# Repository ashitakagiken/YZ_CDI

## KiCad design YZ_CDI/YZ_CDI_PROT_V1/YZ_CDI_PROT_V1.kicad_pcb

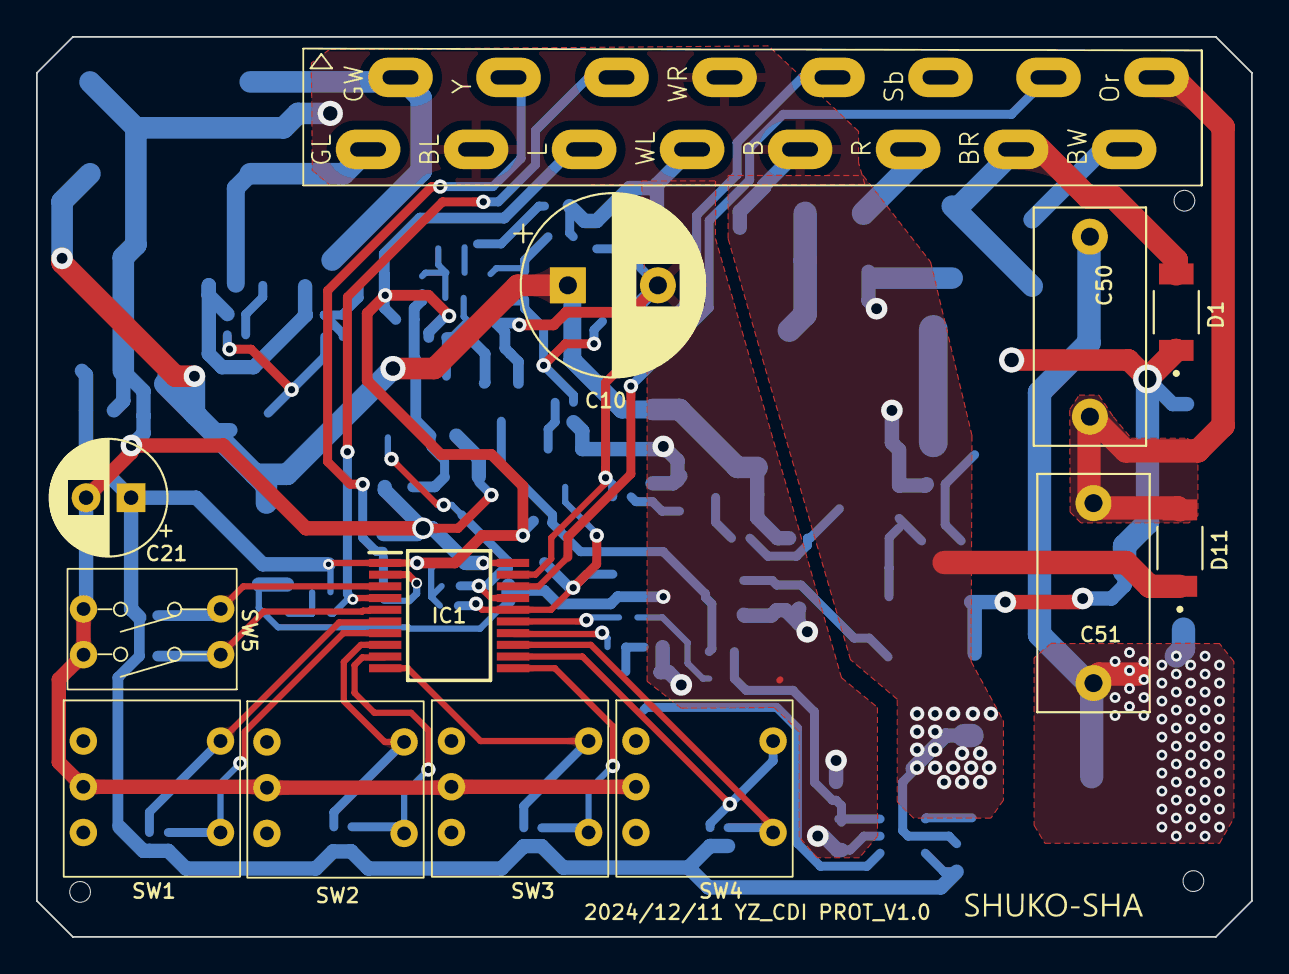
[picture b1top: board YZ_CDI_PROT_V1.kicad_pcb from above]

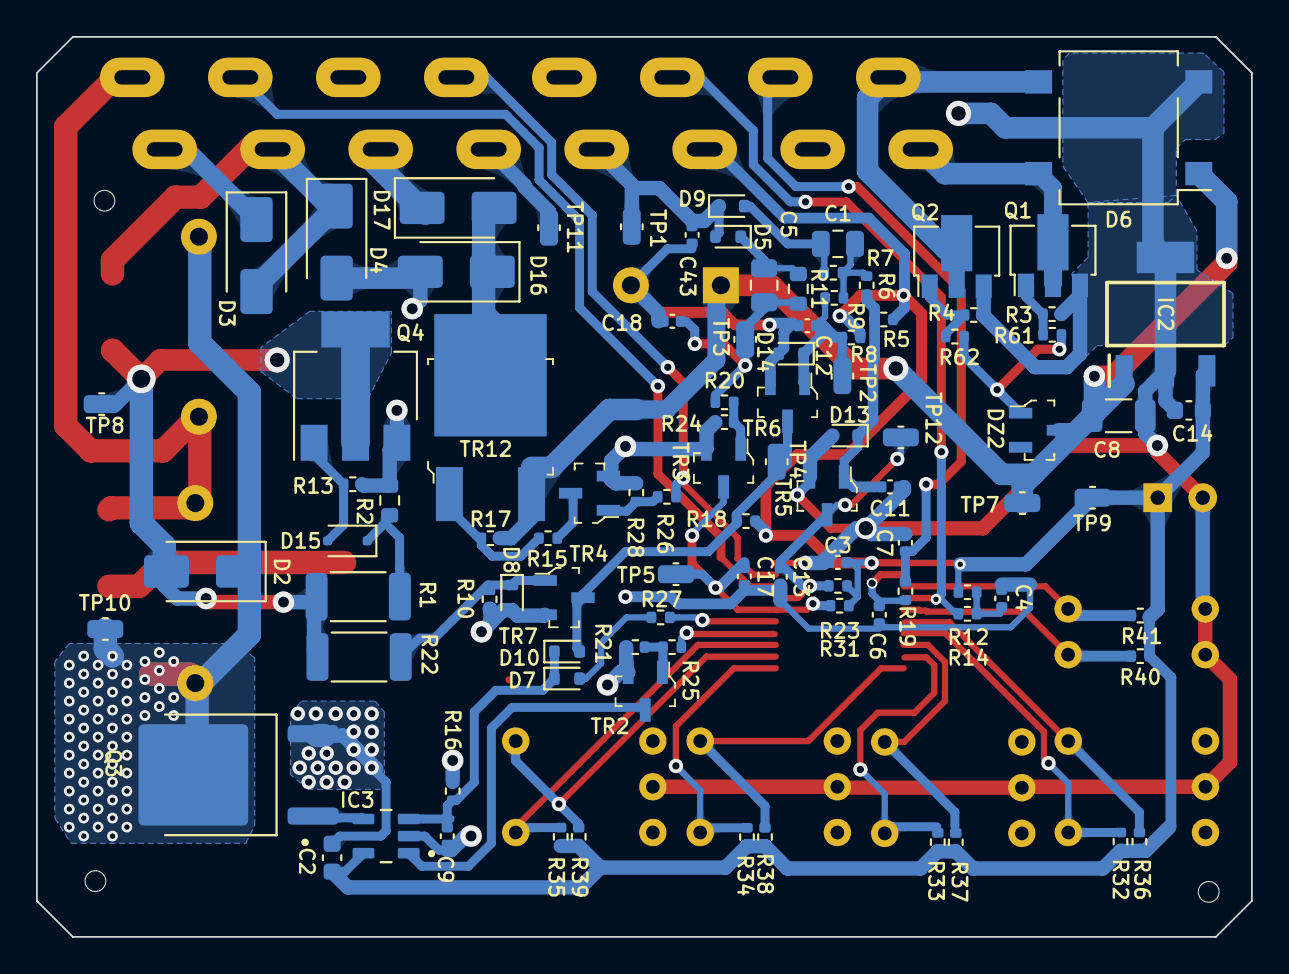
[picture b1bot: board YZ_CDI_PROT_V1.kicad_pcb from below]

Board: 2 copper layers, 67.5 x 50.0 mm, 109 parts (96 on the bottom side), 55 nets.

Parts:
C1: 2.2uF; C_0805_2012Metric
C2: 1uF; C_0603_1608Metric
C3, C6, C7, C11, C12, C17: 0.1uF; C_0402_1005Metric
C4, C9, C13, C18, C43: 10nF; C_0402_1005Metric
C5: 0.47uF; C_0805_2012Metric
C8: 10uF; C_1206_3216Metric
C10: 35V 270uF; CP_Radial_D10.0mm_P5.00mm
C14: 10uF; C_0603_1608Metric
C21: 16V 100uF; CP_Radial_D6.3mm_P2.50mm
C50, C51: 250V 1uF; C_Rect_L13.0mm_W6.0mm_P10.00mm_FKS3_FKP3_MKS4
CN1: FP-C-R16M
D1, D11: TSD3JFSH; SODFL4725X110N
D2, D3, D4, D16, D17: S1J; D_SMA
D5, D7, D8, D9, D10, D13, D14: RB501SM-30FH; D_SOD-523
D6: DF01S; Diode_Bridge_OnSemi_SDIP-4L
D15: BZX100A,115; D_SOD-323F
DZ2: BZX84C9V1LT1G; SOT-23-3
IC1: PIC16F15245-I_SS; SOP65P780X200-20N
IC2: TPS7B6950QDCYRQ1; SOT230P700X180-4N
IC3: UCC27519AQDBVRQ1; SOT95P280X145-5N
Q1, Q2: ZXMN6A11ZTA; SOT-89-3
Q3: RGPR30BM40; DPAK228P990X239-4N
Q4: IPN50R3K0CE; SOT-223-3_TabPin2
R1, R22: 200k 1/2W; R_2010_5025Metric
R2: 200K; R_0603_1608Metric
R3, R4, R12, R32, R33, R34, R35, R36, R37, R38, R39, R40, R41: 10k; R_0402_1005Metric
R5, R8, R13: 15k; R_0402_1005Metric
R6, R9, R15, R18, R27, R31: 2.2k; R_0402_1005Metric
R7: 22k; R_0402_1005Metric
R10, R20, R21, R25, R26, R28, R61, R62: 5.1k; R_0402_1005Metric
R11: 200k; R_0603_1608Metric
R14: 470; R_0402_1005Metric
R16, R17: 4.7k; R_0402_1005Metric
R19: 1k; R_0402_1005Metric
R23: 1.5k; R_0402_1005Metric
R24: 3.3k; R_0402_1005Metric
SW1, SW2, SW3, SW4: 42J04
SW5: EDS102SZ
TP1: WL PU; CheckPoint_1608Metric
TP2: PU2 BASE; CheckPoint_1608Metric
TP3: PU1 BASE; CheckPoint_1608Metric
TP4: PU2 INPUT; CheckPoint_1608Metric
TP5: PU1 INPUT; CheckPoint_1608Metric
TP7: +12V; CheckPoint_1608Metric
TP8: CHG1 OUT; CheckPoint_1608Metric
TP9: +5V; CheckPoint_1608Metric
TP10: CAP CHG; CheckPoint_1608Metric
TP11: GND; CheckPoint_1608Metric
TP12: PU2 MCUIN; CheckPoint_1608Metric
TR2, TR3, TR4, TR5, TR6, TR7: PMBS3904,215; SOT-23-3
TR12: IRFR9024NTRPBF; TO-252-3

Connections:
+5V: C2.1, C3.1, C14.1, C21.1, CN1.6 (L_TPS_REF+), IC1.1 (VDD), IC2.3 (OUT), IC3.5 (VDD), R5.1, R8.1, R12.1, R18.1, R23.1, R31.1, R32.1, R33.1, R34.1, R35.1, R36.2, R37.2, R38.2, R39.2, R40.1, R41.2, TP9.1
+12V: C8.1, C10.1, D6.1 (+), DZ2.3 (K), IC2.1 (IN), R17.1, TP7.1, TR12.3 (S)
/BR: CN1.2 (BR_CHG1), D1.A, D3.2 (A), D4.1 (K)
/BW: CN1.1 (BW_KILL), D3.1 (K)
/CAP+: C50.2, C51.2, D2.1 (K), Q3.2 (D), TP10.1
/CHG: D1.C, D2.2 (A), Q4.2 (D), R1.1, R22.1, TP8.1
/GL: CN1.8 (GL_CHG2-), D6.4, Q1.2 (D)
/GW: CN1.9 (GW_CHG2-), D6.3, Q2.2 (D)
/MCU_IGOUT: IC1.15 (RC1), R27.1
/MCU_PU1IN: C17.1, IC1.16 (RC0), R31.2, TP5.1, TR3.3 (C)
/MCU_PU2DISABLE: IC1.14 (RC2), R25.1
/MCU_PU2IN: C13.1, IC1.17 (RA2), R23.2, TP12.1, TR5.3 (C)
/MCU_TPSIN: C6.1, IC1.2 (RA5), R19.1
/OR: C50.1, C51.1, CN1.16 (OR_IG), D11.A
/PGC: CN1.15 (PGC), IC1.18 (RA1/ICSPCLK)
/PGD: CN1.13 (PGD), IC1.19 (RA0/ICSPDAT), R26.1
/PWJ_SEL: IC1.5 (RC5), R40.2, SW5.1
/R: CN1.3 (R_SOL), D17.1 (K)
/REV_LIMIT_SEL: IC1.3 (RA4), R41.1, SW5.2
/VPP: CN1.11 (Vpp), IC1.4 (~MCLR/VPP/RA3), R14.2
/WL: C43.1, CN1.5 (WL_PU), D5.2 (A), D9.1 (K), TP1.1
/Y: C7.1, CN1.10 (Y_TPS_IN), R19.2
GND: C2.2, C3.2, C4.2, C6.2, C7.2, C8.2, C9.2, C10.2, C11.2, C12.2, C13.2, C14.2, C17.2, C18.2, C21.2, C43.2, CN1.4 (B_GND), CN1.7 (BL_TPS_GND), CN1.12 (WR_PU_GND), D4.2 (A), D6.2 (-), D8.2 (A), D11.C, D13.2 (A), D14.2 (A), D16.2 (A), IC1.20 (VSS), IC2.2 (GND_1), IC2.4 (GND_2), IC3.2 (GND), Q1.3 (S), Q2.3 (S), Q3.3 (S), Q4.3 (S), R2.2, R3.2, R4.2, R10.2, R13.2, R16.2, R21.2, R24.1, R28.2, SW1.3 (COMMON), SW2.3 (COMMON), SW3.3 (COMMON), SW4.3 (COMMON), SW5.3, SW5.4, TP11.1, TR2.2 (E), TR3.2 (E), TR4.2 (E), TR5.2 (E), TR6.2 (E), TR7.2 (E)
unnamed: C1.2, R6.1, R7.2, R9.1
unnamed: C4.1, R12.2, R14.1
unnamed: C5.2, C18.1, R11.2, R20.1, TP3.1
unnamed: C5.1, D5.1 (K), R11.1
unnamed: D7.2 (A), R27.2
unnamed: D8.1 (K), R10.1, R22.2, TR7.1 (B)
unnamed: C1.1, D9.2 (A), R7.1
unnamed: D10.2 (A), R18.2, TP4.1, TR6.3 (C), TR7.3 (C)
unnamed: C9.1, D7.1 (K), D10.1 (K), IC3.3 (IN+), R16.1
unnamed: C11.1, D13.1 (K), R5.2, R6.2, TR5.1 (B)
unnamed: C12.1, D14.1 (K), R8.2, R9.2, TP2.1, TR6.1 (B)
unnamed: D15.2 (A), Q4.1 (G), R13.1
unnamed: D15.1 (K), R1.2, R2.1
unnamed: D16.1 (K), D17.2 (A), TR12.4 (D)
unnamed: DZ2.1 (A), R61.1, R62.1
unnamed: IC1.13 (RB4), R35.2, SW4.2
unnamed: IC1.12 (RB5), R39.1, SW4.1
unnamed: IC1.11 (RB6), R34.2, SW3.2
unnamed: IC1.10 (RB7), R38.1, SW3.1
unnamed: IC1.7 (RC3), R32.2, SW1.2
unnamed: IC1.6 (RC4), R36.1, SW1.1
unnamed: IC1.8 (RC6), R37.1, SW2.1
unnamed: IC1.9 (RC7), R33.2, SW2.2
unnamed: IC3.1 (EN), TR2.3 (C)
unnamed: IC3.4 (OUT), Q3.1 (G)
unnamed: Q1.1 (G), R3.1, R61.2
unnamed: Q2.1 (G), R4.1, R62.2
unnamed: R21.1, R25.2, TR2.1 (B)
unnamed: R20.2, R24.2, TR3.1 (B)
unnamed: R26.2, R28.1, TR4.1 (B)
unnamed: R15.2, TR4.3 (C)
unnamed: R15.1, R17.2, TR12.1 (G)

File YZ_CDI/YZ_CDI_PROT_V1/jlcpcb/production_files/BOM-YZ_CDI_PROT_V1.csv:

Comment,Designator,Footprint,LCSC,Quantity
250V 1uF,C51,C_Rect_L13.0mm_W6.0mm_P10.00mm_FKS3_FKP3_MKS4,,1
250V 1uF,C50,C_Rect_L13.0mm_W6.0mm_P10.00mm_FKS3_FKP3_MKS4,,1
+12V,TP7,CheckPoint_1608Metric,,1
TSD3JFSH,D11,SODFL4725X110N,,1
PU2 BASE,TP2,CheckPoint_1608Metric,,1
FP-C-R16M,CN1,FP-C-R16M,,1
TSD3JFSH,D1,SODFL4725X110N,,1
PIC16F15245-I_SS,IC1,SOP65P780X200-20N,,1
CAP CHG,TP10,CheckPoint_1608Metric,,1
GND,TP11,CheckPoint_1608Metric,,1
42J04,SW2,42J04,,1
+5V,TP9,CheckPoint_1608Metric,,1
PU2 INPUT,TP4,CheckPoint_1608Metric,,1
42J04,SW1,42J04,,1
EDS102SZ,SW5,EDS102SZ,,1
42J04,SW3,42J04,,1
35V 270uF,C10,CP_Radial_D10.0mm_P5.00mm,,1
PU1 BASE,TP3,CheckPoint_1608Metric,,1
16V 100uF,C21,CP_Radial_D6.3mm_P2.50mm,,1
PU1 INPUT,TP5,CheckPoint_1608Metric,,1
PU2 MCUIN,TP12,CheckPoint_1608Metric,,1
42J04,SW4,42J04,,1
WL PU,TP1,CheckPoint_1608Metric,,1
CHG1 OUT,TP8,CheckPoint_1608Metric,,1
PJD1406PA-AU,TR12,TO-252-3,,1
"PMBS3904,215",TR3,SOT-23-3,,1
4.7k,R16,R_0402_1005Metric,,1
10k,R38,R_0402_1005Metric,,1
ZXMN6A11ZTA,Q1,SOT-89-3,,1
10uF,C8,C_0603_1608Metric,,1
22k,R7,R_0402_1005Metric,,1
0.1uF,C6,C_0603_1608Metric,,1
UCC27519AQDBVRQ1,IC3,SOT95P280X145-5N,,1
10k,R33,R_0402_1005Metric,,1
10nF,C43,C_0603_1608Metric,,1
10nF,C18,C_0603_1608Metric,,1
5.1k,R61,R_0402_1005Metric,,1
2.2k,R9,R_0402_1005Metric,,1
RGPR30BM40,Q3,DPAK228P990X239-4N,,1
180k 1/2W,R1,R_2512_6332Metric,,1
0.47uF,C5,C_0603_1608Metric,,1
15k,R8,R_0402_1005Metric,,1
2.2k,R18,R_0402_1005Metric,,1
5.1k,R62,R_0402_1005Metric,,1
1.5k,R23,R_0402_1005Metric,,1
10k,R12,R_0402_1005Metric,,1
TPS7B6950QDCYRQ1,IC2,SOT230P700X180-4N,,1
D5V0H1B2LP-7B,D12,D5V0H1B2LP7B,,1
2.2k,R6,R_0402_1005Metric,,1
RB501SM-30FH,D14,D_SOD-523,,1
10k,R35,R_0402_1005Metric,,1
0.01uF,C9,C_0603_1608Metric,,1
"BZX100A,115",D15,D_SOD-323F,,1
RB501SM-30FH,D13,D_SOD-523,,1
10k,R3,R_0402_1005Metric,,1
0.1uF,C3,C_0603_1608Metric,,1
15k,R5,R_0402_1005Metric,,1
F7A,D17,D_SOD-123FL,,1
10k,R40,R_0402_1005Metric,,1
15k,R13,R_0402_1005Metric,,1
MMUN2232LT1G,TR7,SOT95P237X111-3N,,1
10k,R37,R_0402_1005Metric,,1
2.2k,R15,R_0402_1005Metric,,1
RB501SM-30FH,D5,D_SOD-523,,1
0.01uF,C13,C_0603_1608Metric,,1
SBS25,D6,DIOB_SBS25,,1
0.1uF,C11,C_0603_1608Metric,,1
MMUN2232LT1G,TR1,SOT95P237X111-3N,,1
0.1uF,C12,C_0603_1608Metric,,1
10uF,C14,C_0603_1608Metric,,1
RB501SM-30FH,D10,D_SOD-523,,1
10nF,C4,C_0603_1608Metric,,1
MMUN2232LT1G,TR2,SOT95P237X111-3N,,1
TSD3JFSH,D2,SODFL4725X110N,,1
470,R14,R_0402_1005Metric,,1
10k,R39,R_0402_1005Metric,,1
"PMBS3904,215",TR6,SOT-23-3,,1
180K,R2,R_0402_1005Metric,,1
10k,R4,R_0402_1005Metric,,1
ZXMN6A11ZTA,Q2,SOT-89-3,,1
RB501SM-30FH,D8,D_SOD-523,,1
1uF,C2,C_0603_1608Metric,,1
F7A,D16,D_SOD-123FL,,1
RB501SM-30FH,D9,D_SOD-523,,1
2.2k,R27,R_0402_1005Metric,,1
1k,R19,R_0402_1005Metric,,1
10k,R36,R_0402_1005Metric,,1
RB501SM-30FH,D7,D_SOD-523,,1
BZX84C9V1LT1G,DZ2,SOT-23-3,,1
2.2k,R31,R_0402_1005Metric,,1
5.6k,R20,R_0402_1005Metric,,1
F7A,D3,D_SOD-123FL,,1
0.1u,C17,C_0603_1608Metric,,1
150k 1W,R22,R_2512_6332Metric,,1
IPN50R2K0CEATMA1,Q4,SOT-223-3_TabPin2,,1
4.7k,R17,R_0402_1005Metric,,1
"PMBS3904,215",TR5,SOT-23-3,,1
3.3k,R24,R_0402_1005Metric,,1
2.2uF,C1,C_1206_3216Metric,,1
10k,R41,R_0402_1005Metric,,1
180k,R11,R_0402_1005Metric,,1
10k,R34,R_0402_1005Metric,,1
F7A,D4,D_SOD-123FL,,1
0.1uF,C7,C_0603_1608Metric,,1
10k,R32,R_0402_1005Metric,,1

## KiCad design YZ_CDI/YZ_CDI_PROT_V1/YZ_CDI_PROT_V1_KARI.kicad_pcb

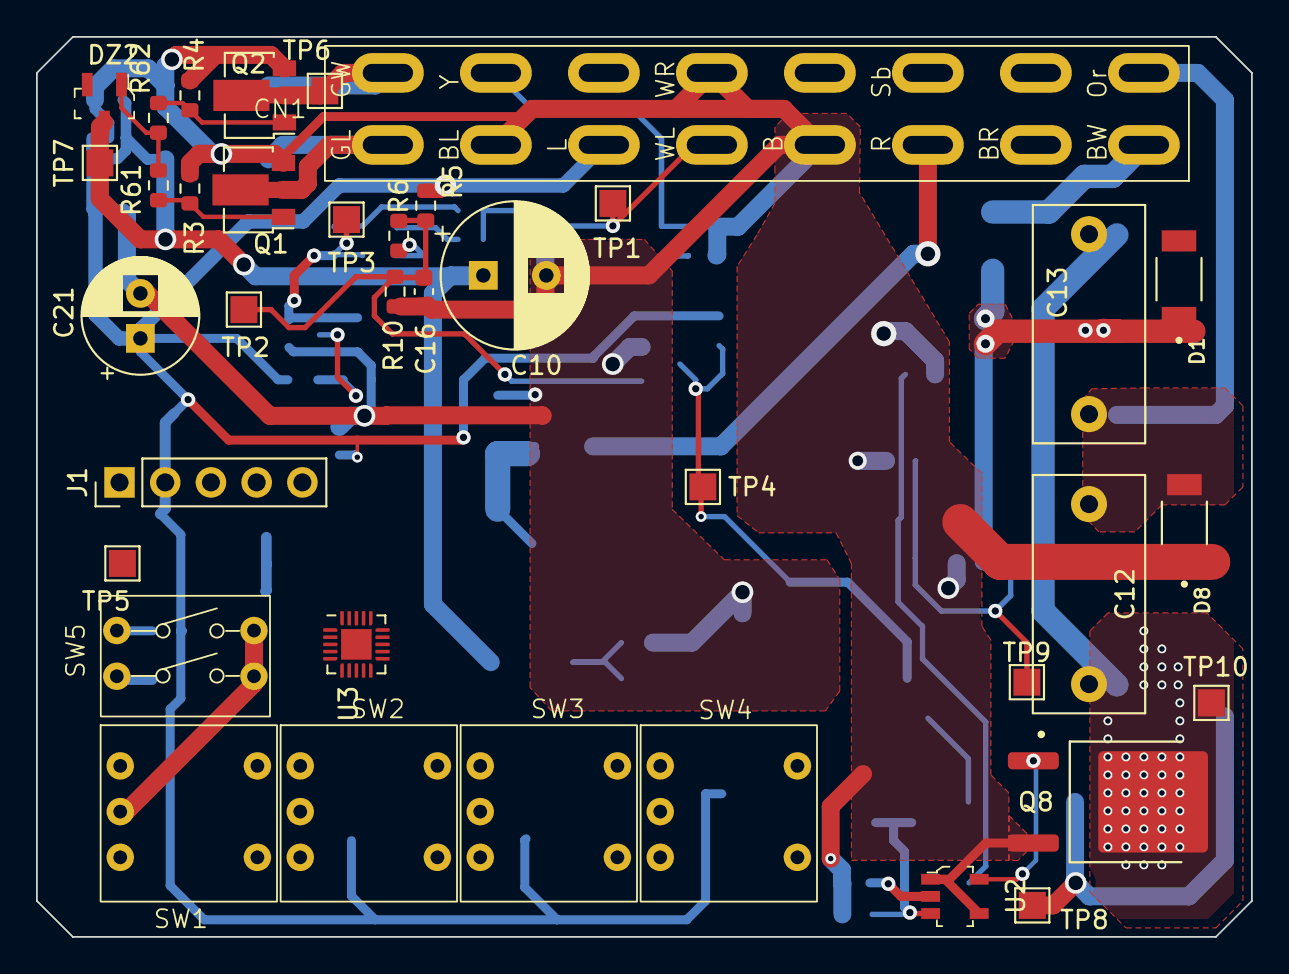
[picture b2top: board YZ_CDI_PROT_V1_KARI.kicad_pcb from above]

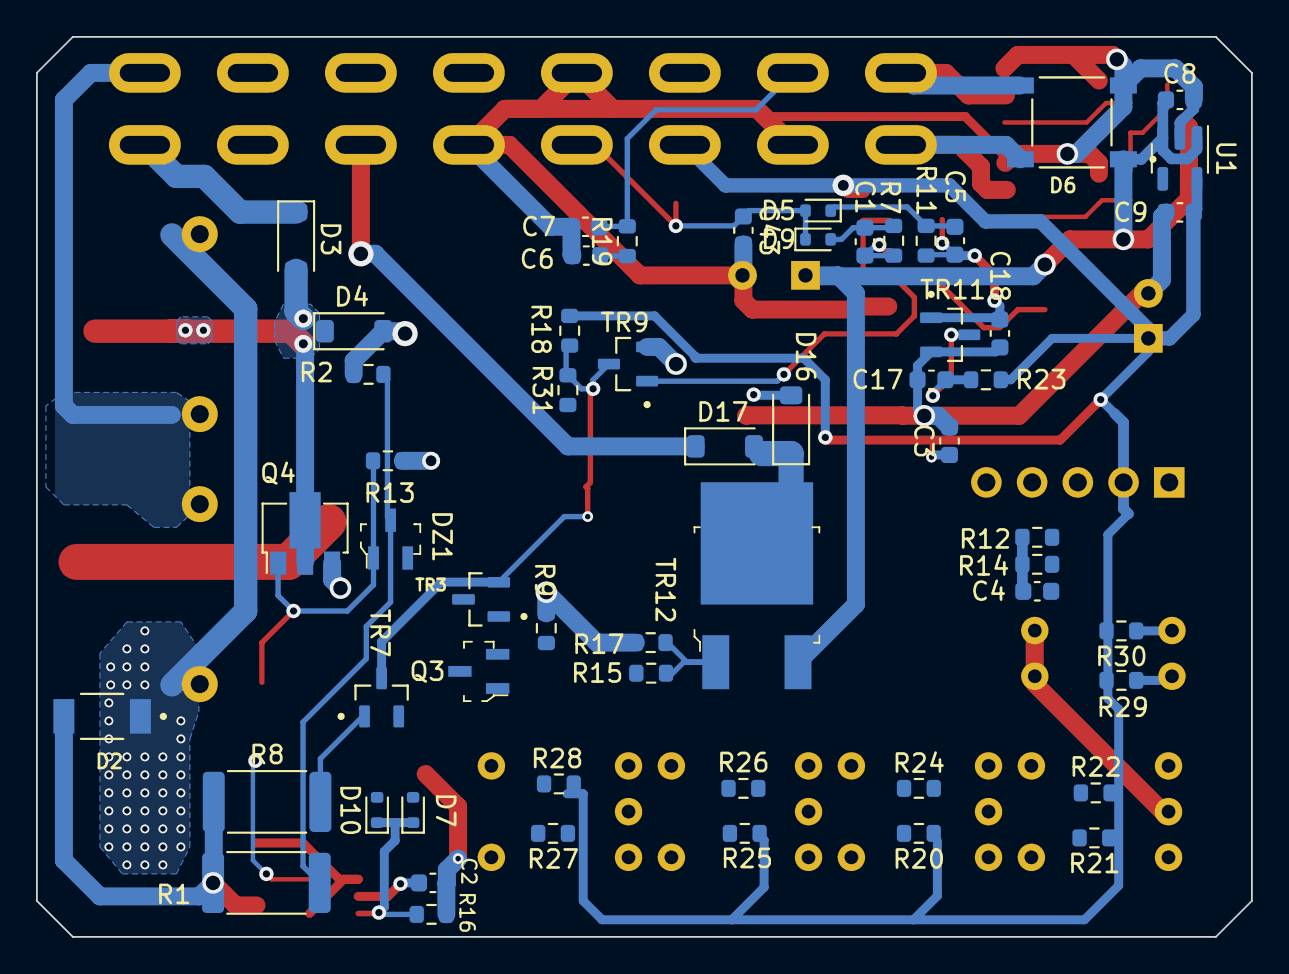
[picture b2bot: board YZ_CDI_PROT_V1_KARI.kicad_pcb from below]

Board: 2 copper layers, 67.5 x 50.0 mm, 94 parts (57 on the bottom side), 51 nets.

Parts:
C1: 1u; C_0603_1608Metric
C2, C8, C9, C17: 0.1u; C_0603_1608Metric
C3, C6, C7: 0.1uF; C_0603_1608Metric
C4, C16, C18, C43: 10nF; C_0603_1608Metric
C5: 0.47u; C_0603_1608Metric
C10: 35V 100uF; CP_Radial_D8.0mm_P3.50mm
C12, C13: 250V 1uF; C_Rect_L13.0mm_W6.0mm_P10.00mm_FKS3_FKP3_MKS4
C21: 16V 100uF; CP_Radial_D6.3mm_P2.50mm
CN1: FP-C-R16M
D1, D2, D8: TSD3JFSH; SODFL4725X110N
D3, D4, D16, D17: F7A; D_SOD-123FL
D5, D7, D9, D10: RB501SM-30FH; D_SOD-523
D6: SBS25; DIOB_SBS25
DZ1: SZMMBZ5270BLT1G; SOT-23-3
DZ2: BZX84-C9V1,215; SOT-23-3
J1: PICKIT; PinHeader_1x05_P2.54mm_Vertical
Q1: 2SK4017; SOT-89-3
Q2, Q4: TBD; SOT-89-3
Q3: MMUN2132LT1G; SOT-23-3
Q8: RGPR30BM40; DPAK228P990X239-4N
R1: 180k 1/2W; R_2512_6332Metric
R2: 180K; R_0603_1608Metric
R3, R4, R13, R61, R62: TBD; R_0603_1608Metric
R5: 15k; R_0603_1608Metric
R6, R19, R31: 1k; R_0603_1608Metric
R7, R10: 22k; R_0603_1608Metric
R8: 150k 1W; R_2512_6332Metric
R9: 100K; R_0603_1608Metric
R11: 180k; R_0603_1608Metric
R12, R16, R17, R20, R21, R22, R24, R25, R26, R27, R28, R29, R30: 10k; R_0603_1608Metric
R14, R15: 120; R_0603_1608Metric
R18, R23: 2.2k; R_0603_1608Metric
SW1, SW2, SW3, SW4: 42J04
SW5: EDS102SZ
TP1: WL PU; TestPoint_Pad_1.5x1.5mm
TP2: PU2 BASE; TestPoint_Pad_1.5x1.5mm
TP3: PU1 BASE; TestPoint_Pad_1.5x1.5mm
TP4: PU2 INPUT; TestPoint_Pad_1.5x1.5mm
TP5: PU1 INPUT; TestPoint_Pad_1.5x1.5mm
TP6: GW DC; TestPoint_Pad_1.5x1.5mm
TP7: +12V; TestPoint_Pad_1.5x1.5mm
TP8: CHG1 OUT; TestPoint_Pad_1.5x1.5mm
TP9: CHG1 REG GATE; TestPoint_Pad_1.5x1.5mm
TP10: CAP CHG; TestPoint_Pad_1.5x1.5mm
TR3: PMBS3906,215; SOT95P230X110-3N
TR7, TR11: MMUN2232LT1G; SOT95P237X111-3N
TR9: PMBS3904,215; SOT95P237X111-3N
TR12: Q_PMOS_GDS; TO-252-3
U1: TPS78450QDBVRQ1; SOT-23-5
U2: MCP1402T-E_OT; SOT-753
U3: PIC16F15245; VQFN-20-1EP_3x3mm_P0.4mm_EP1.7x1.7mm

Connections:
+5V: C2.1, C3.1, C9.1, C21.1, CN1.6 (L_TPS_REF+), J1.2, Q3.2 (E), R5.1, R12.1, R18.1, R20.1, R21.1, R22.2, R23.1, R24.2, R25.1, R26.2, R27.1, R28.2, R29.1, R30.2, U1.5 (OUT), U2.2 (VDD), U3.18 (VDD)
+12V: C8.1, C10.1, D6.+, DZ2.3 (K), TP7.1, TR12.3 (S), U1.1 (IN), U1.3 (EN)
/BR: CN1.2 (BR_CHG1), D1.A
/BW: CN1.1 (BW_KILL), D3.1 (K)
/CAP+: C12.2, C13.2, D2.C, Q8.2 (D), TP10.1
/CHG: D1.C, D2.A, D3.2 (A), D4.1 (K), Q4.2 (D), R1.1, R8.1, TP8.1
/GL: CN1.8 (GL_CHG2-), D6.AC1, Q1.2 (D)
/GW: CN1.9 (GW_CHG2-), D6.AC2, Q2.2 (D), TP6.1
/MCU_IGOUT: Q3.1 (B), U3.20 (RA4)
/MCU_PU1IN: C17.1, R23.2, TP5.1, TR11.3 (C), U3.3 (RC4)
/MCU_PU2IN: R31.1, U3.2 (RC5)
/MCU_SOLOUT: R15.2, U3.19 (RA5)
/MCU_TPSIN: C6.1, R19.1, U3.14 (RA2)
/OR: C12.1, C13.1, CN1.16 (OR_IG), D8.A
/PGC: J1.5, U3.15 (RA1/ICSPCLK)
/PGD: J1.4, U3.16 (RA0/ICSPDAT)
/PWJ_SEL: R29.2, SW5.2, U3.5 (RC6)
/R: CN1.3 (R_SOL), D17.1 (K)
/REV_LIMIT_SEL: R30.1, SW5.1, U3.4 (RC3)
/VPP: J1.1, R14.2, U3.1 (MCLR/RA3)
/WL: C43.1, CN1.5 (WL_PU), D5.2 (A), D9.1 (K), TP1.1
/Y: C7.1, CN1.10 (Y_TPS_IN), R19.2
GND: C2.2, C3.2, C4.2, C6.2, C7.2, C8.2, C9.2, C10.2, C16.2, C17.2, C18.2, C21.2, C43.2, CN1.4 (B_GND), CN1.7 (BL_TPS_GND), CN1.12 (WR_PU_GND), D4.2 (A), D6.-, D8.C, D16.2 (A), J1.3, Q1.3 (S), Q2.3 (S), Q4.3 (S), Q8.3 (S), R2.2, R3.2, R4.2, R9.2, R10.2, R13.2, R16.2, R17.2, SW1.3 (COMMON), SW2.3 (COMMON), SW3.3 (COMMON), SW4.3 (COMMON), SW5.3, SW5.4, TR7.2 (E), TR9.2 (E), TR11.2 (E), U1.2 (GND), U2.1 (GND), U2.4 (GND), U3.17 (VSS)
unnamed: C1.2, R6.1, R7.2
unnamed: C4.1, R12.2, R14.1
unnamed: C5.1, D5.1 (K), R11.1
unnamed: D7.2 (A), Q3.3 (C)
unnamed: C1.1, D9.2 (A), R7.1
unnamed: D10.2 (A), TR3.3 (C)
unnamed: D7.1 (K), D10.1 (K), R16.1, U2.3 (IN)
unnamed: D16.1 (K), D17.2 (A), TR12.4 (D)
unnamed: DZ1.1 (A), Q4.1 (G), R13.1, TP9.1
unnamed: DZ1.3 (K), R1.2, R2.1
unnamed: DZ2.1 (A), R61.1, R62.1
unnamed: Q1.1 (G), R3.1, R61.2
unnamed: Q2.1 (G), R4.1, R62.2
unnamed: Q8.1 (G), U2.5 (OUT)
unnamed: R9.1, TR3.1 (B)
unnamed: R18.2, R31.2, TP4.1, TR3.2 (E), TR7.3 (C), TR9.3 (C)
unnamed: R8.2, TR7.1 (B)
unnamed: C16.1, R5.2, R6.2, R10.1, TP2.1, TR9.1 (B)
unnamed: C5.2, C18.1, R11.2, TP3.1, TR11.1 (B)
unnamed: R15.1, R17.1, TR12.1 (G)
unnamed: R26.1, SW3.1, U3.10 (RB4)
unnamed: R20.2, SW2.2, U3.9 (RB5)
unnamed: R24.1, SW2.1, U3.8 (RB6)
unnamed: R21.2, SW1.2, U3.7 (RB7)
unnamed: R27.2, SW4.2, U3.13 (RC0)
unnamed: R28.1, SW4.1, U3.12 (RC1)
unnamed: R25.2, SW3.2, U3.11 (RC2)
unnamed: R22.1, SW1.1, U3.6 (RC7)

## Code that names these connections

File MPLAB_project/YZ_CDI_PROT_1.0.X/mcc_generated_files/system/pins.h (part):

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// get/set IO_RA0 aliases
#define IO_RA0_TRIS                 TRISAbits.TRISA0
#define IO_RA0_LAT                  LATAbits.LATA0
#define IO_RA0_PORT                 PORTAbits.RA0
#define IO_RA0_WPU                  WPUAbits.WPUA0
#define IO_RA0_OD                   ODCONAbits.ODCA0
#define IO_RA0_ANS                  ANSELAbits.ANSA0
#define IO_RA0_SetHigh()            do { LATAbits.LATA0 = 1; } while(0)
#define IO_RA0_SetLow()             do { LATAbits.LATA0 = 0; } while(0)
#define IO_RA0_Toggle()             do { LATAbits.LATA0 = ~LATAbits.LATA0; } while(0)
#define IO_RA0_GetValue()           PORTAbits.RA0
#define IO_RA0_SetDigitalInput()    do { TRISAbits.TRISA0 = 1; } while(0)
#define IO_RA0_SetDigitalOutput()   do { TRISAbits.TRISA0 = 0; } while(0)
#define IO_RA0_SetPullup()          do { WPUAbits.WPUA0 = 1; } while(0)
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// get/set IO_RA1 aliases
#define IO_RA1_TRIS                 TRISAbits.TRISA1
#define IO_RA1_LAT                  LATAbits.LATA1
#define IO_RA1_PORT                 PORTAbits.RA1
#define IO_RA1_WPU                  WPUAbits.WPUA1
#define IO_RA1_OD                   ODCONAbits.ODCA1
#define IO_RA1_ANS                  ANSELAbits.ANSA1
#define IO_RA1_SetHigh()            do { LATAbits.LATA1 = 1; } while(0)
#define IO_RA1_SetLow()             do { LATAbits.LATA1 = 0; } while(0)
#define IO_RA1_Toggle()             do { LATAbits.LATA1 = ~LATAbits.LATA1; } while(0)
#define IO_RA1_GetValue()           PORTAbits.RA1
#define IO_RA1_SetDigitalInput()    do { TRISAbits.TRISA1 = 1; } while(0)
#define IO_RA1_SetDigitalOutput()   do { TRISAbits.TRISA1 = 0; } while(0)
#define IO_RA1_SetPullup()          do { WPUAbits.WPUA1 = 1; } while(0)
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// get/set IO_RA2 aliases
#define IO_RA2_TRIS                 TRISAbits.TRISA2
#define IO_RA2_LAT                  LATAbits.LATA2
#define IO_RA2_PORT                 PORTAbits.RA2
#define IO_RA2_WPU                  WPUAbits.WPUA2
#define IO_RA2_OD                   ODCONAbits.ODCA2
#define IO_RA2_ANS                  ANSELAbits.ANSA2
#define IO_RA2_SetHigh()            do { LATAbits.LATA2 = 1; } while(0)
#define IO_RA2_SetLow()             do { LATAbits.LATA2 = 0; } while(0)
#define IO_RA2_Toggle()             do { LATAbits.LATA2 = ~LATAbits.LATA2; } while(0)
#define IO_RA2_GetValue()           PORTAbits.RA2
#define IO_RA2_SetDigitalInput()    do { TRISAbits.TRISA2 = 1; } while(0)
#define IO_RA2_SetDigitalOutput()   do { TRISAbits.TRISA2 = 0; } while(0)
#define IO_RA2_SetPullup()          do { WPUAbits.WPUA2 = 1; } while(0)
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// get/set IO_RA4 aliases
#define IO_RA4_TRIS                 TRISAbits.TRISA4
#define IO_RA4_LAT                  LATAbits.LATA4
#define IO_RA4_PORT                 PORTAbits.RA4
#define IO_RA4_WPU                  WPUAbits.WPUA4
#define IO_RA4_OD                   ODCONAbits.ODCA4
#define IO_RA4_ANS                  ANSELAbits.ANSA4
#define IO_RA4_SetHigh()            do { LATAbits.LATA4 = 1; } while(0)
#define IO_RA4_SetLow()             do { LATAbits.LATA4 = 0; } while(0)
#define IO_RA4_Toggle()             do { LATAbits.LATA4 = ~LATAbits.LATA4; } while(0)
#define IO_RA4_GetValue()           PORTAbits.RA4
#define IO_RA4_SetDigitalInput()    do { TRISAbits.TRISA4 = 1; } while(0)
#define IO_RA4_SetDigitalOutput()   do { TRISAbits.TRISA4 = 0; } while(0)
#define IO_RA4_SetPullup()          do { WPUAbits.WPUA4 = 1; } while(0)
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// get/set IO_RA5 aliases
#define IO_RA5_TRIS                 TRISAbits.TRISA5
#define IO_RA5_LAT                  LATAbits.LATA5
#define IO_RA5_PORT                 PORTAbits.RA5
#define IO_RA5_WPU                  WPUAbits.WPUA5
#define IO_RA5_OD                   ODCONAbits.ODCA5
#define IO_RA5_ANS                  ANSELAbits.ANSA5
#define IO_RA5_SetHigh()            do { LATAbits.LATA5 = 1; } while(0)
#define IO_RA5_SetLow()             do { LATAbits.LATA5 = 0; } while(0)
#define IO_RA5_Toggle()             do { LATAbits.LATA5 = ~LATAbits.LATA5; } while(0)
#define IO_RA5_GetValue()           PORTAbits.RA5
#define IO_RA5_SetDigitalInput()    do { TRISAbits.TRISA5 = 1; } while(0)
#define IO_RA5_SetDigitalOutput()   do { TRISAbits.TRISA5 = 0; } while(0)
#define IO_RA5_SetPullup()          do { WPUAbits.WPUA5 = 1; } while(0)
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// get/set IO_RB4 aliases
#define IO_RB4_TRIS                 TRISBbits.TRISB4
#define IO_RB4_LAT                  LATBbits.LATB4
#define IO_RB4_PORT                 PORTBbits.RB4
#define IO_RB4_WPU                  WPUBbits.WPUB4
#define IO_RB4_OD                   ODCONBbits.ODCB4
#define IO_RB4_ANS                  ANSELBbits.ANSB4
#define IO_RB4_SetHigh()            do { LATBbits.LATB4 = 1; } while(0)
#define IO_RB4_SetLow()             do { LATBbits.LATB4 = 0; } while(0)
#define IO_RB4_Toggle()             do { LATBbits.LATB4 = ~LATBbits.LATB4; } while(0)
#define IO_RB4_GetValue()           PORTBbits.RB4
#define IO_RB4_SetDigitalInput()    do { TRISBbits.TRISB4 = 1; } while(0)
#define IO_RB4_SetDigitalOutput()   do { TRISBbits.TRISB4 = 0; } while(0)
#define IO_RB4_SetPullup()          do { WPUBbits.WPUB4 = 1; } while(0)
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// get/set IO_RB5 aliases
#define IO_RB5_TRIS                 TRISBbits.TRISB5
#define IO_RB5_LAT                  LATBbits.LATB5
#define IO_RB5_PORT                 PORTBbits.RB5
#define IO_RB5_WPU                  WPUBbits.WPUB5
#define IO_RB5_OD                   ODCONBbits.ODCB5
#define IO_RB5_ANS                  ANSELBbits.ANSB5
#define IO_RB5_SetHigh()            do { LATBbits.LATB5 = 1; } while(0)
#define IO_RB5_SetLow()             do { LATBbits.LATB5 = 0; } while(0)
#define IO_RB5_Toggle()             do { LATBbits.LATB5 = ~LATBbits.LATB5; } while(0)
#define IO_RB5_GetValue()           PORTBbits.RB5
#define IO_RB5_SetDigitalInput()    do { TRISBbits.TRISB5 = 1; } while(0)
#define IO_RB5_SetDigitalOutput()   do { TRISBbits.TRISB5 = 0; } while(0)
#define IO_RB5_SetPullup()          do { WPUBbits.WPUB5 = 1; } while(0)
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// get/set IO_RB6 aliases
#define IO_RB6_TRIS                 TRISBbits.TRISB6
#define IO_RB6_LAT                  LATBbits.LATB6
#define IO_RB6_PORT                 PORTBbits.RB6
#define IO_RB6_WPU                  WPUBbits.WPUB6
#define IO_RB6_OD                   ODCONBbits.ODCB6
#define IO_RB6_ANS                  ANSELBbits.ANSB6
#define IO_RB6_SetHigh()            do { LATBbits.LATB6 = 1; } while(0)
#define IO_RB6_SetLow()             do { LATBbits.LATB6 = 0; } while(0)
#define IO_RB6_Toggle()             do { LATBbits.LATB6 = ~LATBbits.LATB6; } while(0)
#define IO_RB6_GetValue()           PORTBbits.RB6
#define IO_RB6_SetDigitalInput()    do { TRISBbits.TRISB6 = 1; } while(0)
#define IO_RB6_SetDigitalOutput()   do { TRISBbits.TRISB6 = 0; } while(0)
#define IO_RB6_SetPullup()          do { WPUBbits.WPUB6 = 1; } while(0)
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// get/set IO_RB7 aliases
#define IO_RB7_TRIS                 TRISBbits.TRISB7
#define IO_RB7_LAT                  LATBbits.LATB7
#define IO_RB7_PORT                 PORTBbits.RB7
#define IO_RB7_WPU                  WPUBbits.WPUB7
#define IO_RB7_OD                   ODCONBbits.ODCB7
#define IO_RB7_ANS                  ANSELBbits.ANSB7
#define IO_RB7_SetHigh()            do { LATBbits.LATB7 = 1; } while(0)
#define IO_RB7_SetLow()             do { LATBbits.LATB7 = 0; } while(0)
#define IO_RB7_Toggle()             do { LATBbits.LATB7 = ~LATBbits.LATB7; } while(0)
#define IO_RB7_GetValue()           PORTBbits.RB7
#define IO_RB7_SetDigitalInput()    do { TRISBbits.TRISB7 = 1; } while(0)
#define IO_RB7_SetDigitalOutput()   do { TRISBbits.TRISB7 = 0; } while(0)
#define IO_RB7_SetPullup()          do { WPUBbits.WPUB7 = 1; } while(0)
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// get/set IO_RC0 aliases
#define IO_RC0_TRIS                 TRISCbits.TRISC0
#define IO_RC0_LAT                  LATCbits.LATC0
#define IO_RC0_PORT                 PORTCbits.RC0
#define IO_RC0_WPU                  WPUCbits.WPUC0
#define IO_RC0_OD                   ODCONCbits.ODCC0
#define IO_RC0_ANS                  ANSELCbits.ANSC0
#define IO_RC0_SetHigh()            do { LATCbits.LATC0 = 1; } while(0)
#define IO_RC0_SetLow()             do { LATCbits.LATC0 = 0; } while(0)
#define IO_RC0_Toggle()             do { LATCbits.LATC0 = ~LATCbits.LATC0; } while(0)
#define IO_RC0_GetValue()           PORTCbits.RC0
#define IO_RC0_SetDigitalInput()    do { TRISCbits.TRISC0 = 1; } while(0)
#define IO_RC0_SetDigitalOutput()   do { TRISCbits.TRISC0 = 0; } while(0)
#define IO_RC0_SetPullup()          do { WPUCbits.WPUC0 = 1; } while(0)
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// get/set IO_RC1 aliases
#define IO_RC1_TRIS                 TRISCbits.TRISC1
#define IO_RC1_LAT                  LATCbits.LATC1
#define IO_RC1_PORT                 PORTCbits.RC1
#define IO_RC1_WPU                  WPUCbits.WPUC1
#define IO_RC1_OD                   ODCONCbits.ODCC1
#define IO_RC1_ANS                  ANSELCbits.ANSC1
#define IO_RC1_SetHigh()            do { LATCbits.LATC1 = 1; } while(0)
#define IO_RC1_SetLow()             do { LATCbits.LATC1 = 0; } while(0)
#define IO_RC1_Toggle()             do { LATCbits.LATC1 = ~LATCbits.LATC1; } while(0)
#define IO_RC1_GetValue()           PORTCbits.RC1
#define IO_RC1_SetDigitalInput()    do { TRISCbits.TRISC1 = 1; } while(0)
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
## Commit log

2025-02-08 test1
2025-02-08 test3
2025-02-08 FIRST TEST FOR MASATERU YZ125
2025-02-08 FIRST TEST FOR YZ250
2025-02-08 IGNITION TABLE CHANGE FOR YZ250
2025-02-08 UART test とりあえずHellow送信完了
2025-02-09 UART test 数値を文字列に変換して送信できるようになった
2025-02-09 UART test 各種データをPCに送付してCPLTで表示できるようになった
2025-02-09 UART test ボーレート57.6k OK
2025-02-09 UART test CCPR2のフラグ解除タイミングで動作不安定？リセット？する問題対処中
2025-02-09 UART test UARTで低回転リセットが観測される問題はいったん放置。オシロでの出力は正常なため。レブリミット修正中
2025-02-09 UART test コミットテスト
2025-02-09 レブリミット修正版
2025-02-10 1500以下でCCP1割り込みはいらない不具合修正中
2025-02-10 1500以下でCCP1割り込みはいらない不具合修正完了。2/11実装テスト実施。
2025-02-12 2/11 watanohaテスト仕様。4000以下でマップ書き換えると回転数検知がばらつき失火するので、運転中マップ書き換えをオミットした。これでとりあえず良好動作版。
